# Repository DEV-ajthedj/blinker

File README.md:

# Blinker
A board that performs a simple blinking sequence of 10 LEDs based on an analog input of your own choosing. This board is dedicated to my mom, as I wanted to give her something cool for her birthday.

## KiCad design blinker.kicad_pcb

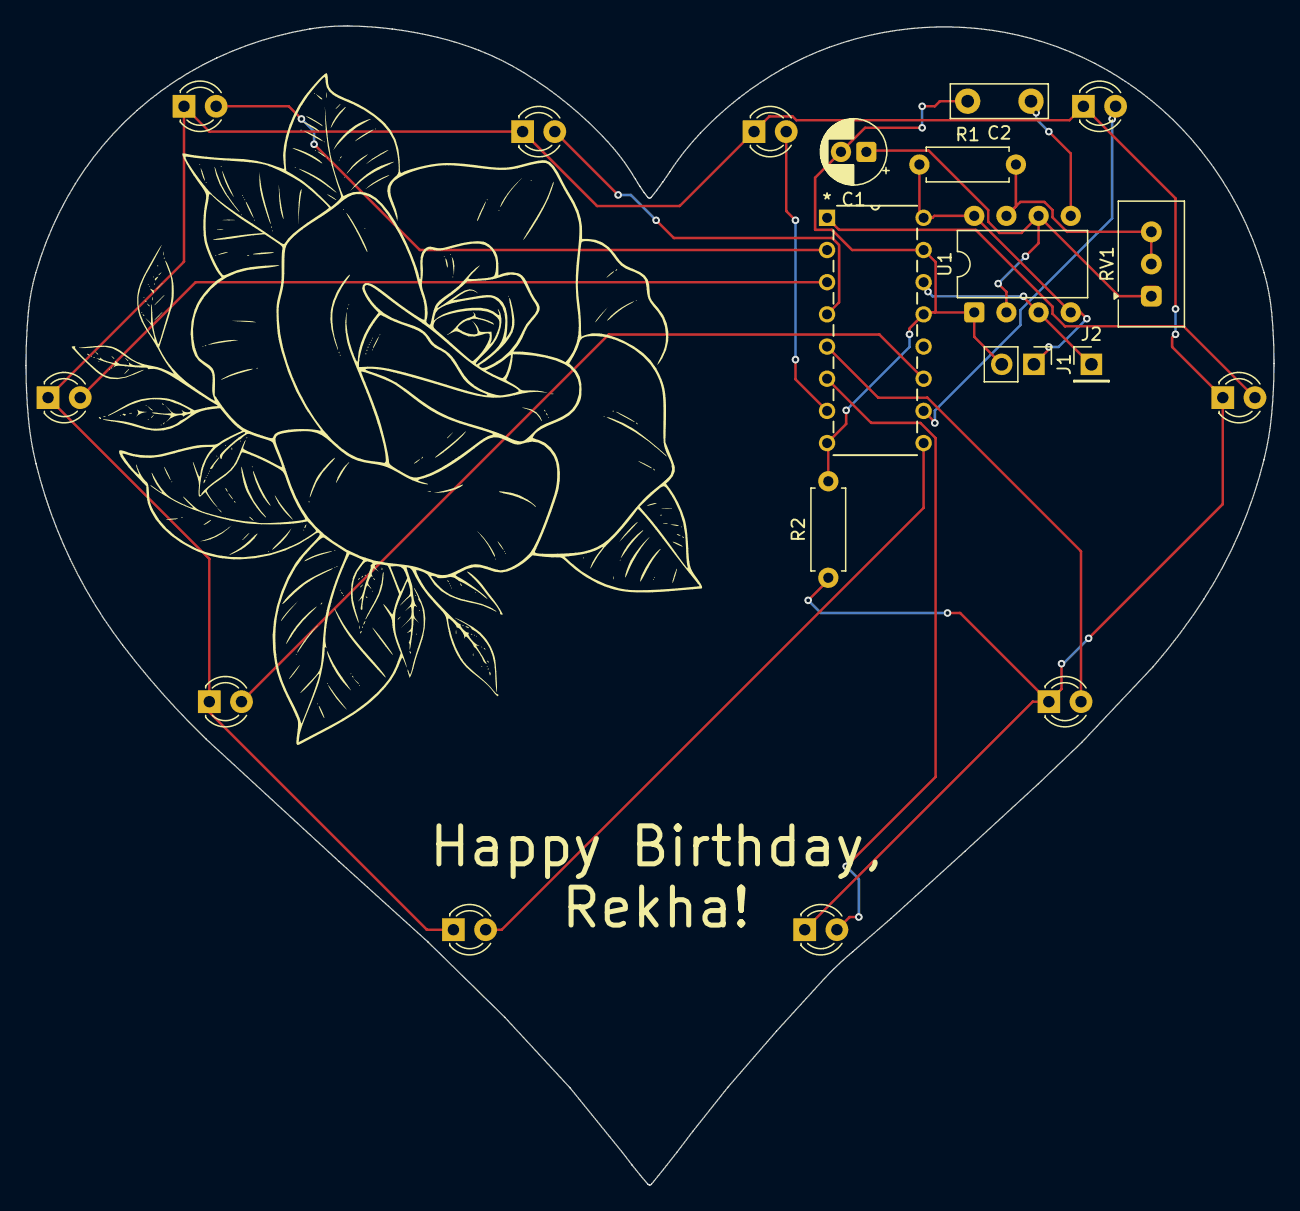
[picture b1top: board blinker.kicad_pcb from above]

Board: 2 copper layers, 98.5 x 91.5 mm, 19 parts (0 on the bottom side), 17 nets.

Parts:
C1: 1 uF; CP_Radial_D5.0mm_P2.00mm
C2: 0.01 uF; C_Disc_D7.5mm_W2.5mm_P5.00mm
D1, D2, D3, D4, D5, D6, D7, D8, D9, D10: LED_D3.0mm
J1: Conn_01x02_Socket; PinHeader_1x02_P2.54mm_Vertical
J2: Conn_01x01_Socket; PinHeader_1x01_P2.54mm_Vertical
R1: 1k; R_Axial_DIN0207_L6.3mm_D2.5mm_P7.62mm_Horizontal
R2: 470; R_Axial_DIN0207_L6.3mm_D2.5mm_P7.62mm_Horizontal
RV1: 50k; Potentiometer_Vishay_T93YA_Vertical
U1: NE555P; DIP-8_W7.62mm
U2: 4017; N16

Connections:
+5V: J1.1, R1.1, U1.4 (~RST), U1.8 (VCC), U2.16 (VDD)
GND: C1.2, C2.2, J1.2, R2.2, U1.1 (GND), U2.8 (VSS), U2.13 (CKEN), U2.15 (Reset)
unnamed: D1.2 (A), U2.3 (Q0)
unnamed: D1.1 (K), D2.1 (K), D3.1 (K), D4.1 (K), D5.1 (K), D6.1 (K), D7.1 (K), D8.1 (K), D9.1 (K), D10.1 (K), R2.1
unnamed: D2.2 (A), U2.2 (Q1)
unnamed: D3.2 (A), U2.4 (Q2)
unnamed: D4.2 (A), U2.7 (Q3)
unnamed: D5.2 (A), U2.10 (Q4)
unnamed: D6.2 (A), U2.1 (Q5)
unnamed: D7.2 (A), U2.5 (Q6)
unnamed: D8.2 (A), U2.6 (Q7)
unnamed: D9.2 (A), U2.9 (Q8)
unnamed: D10.2 (A), U2.11 (Q9)
unnamed: C2.1, U1.5 (CONT)
unnamed: R1.2, RV1.2, RV1.3, U1.7 (DISCH)
OUT: J2.1 (Pin_1_1), U1.3 (OUT), U2.14 (CLK)
TR: C1.1, RV1.1, U1.2 (TRIG), U1.6 (THRES)

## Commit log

2026-04-16 Fix capitalization of project title in README and add image.
    Corrected the capitalization of the project title.
2026-04-16 Update README with dedication for mom's birthday
    Added a personal dedication to the project in the README.
